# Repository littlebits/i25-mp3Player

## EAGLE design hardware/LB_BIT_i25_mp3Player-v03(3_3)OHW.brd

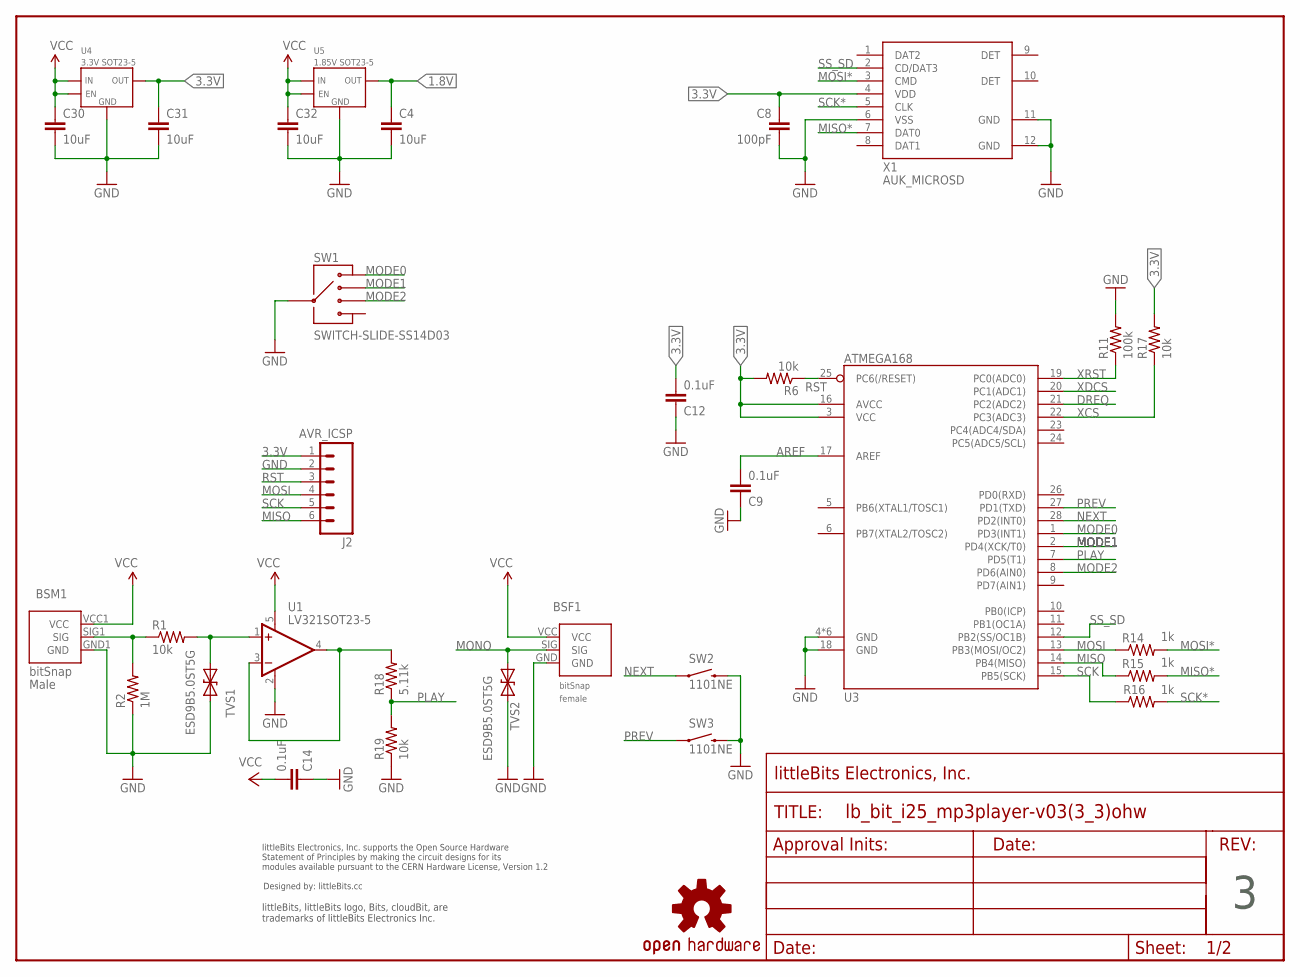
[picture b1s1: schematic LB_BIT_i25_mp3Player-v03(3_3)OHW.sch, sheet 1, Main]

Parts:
BSF1: BITSNAP_V03_FEMALE
BSM1: BITSNAP_V03_MALE
C4, C30, C31, C32: 10uF; CAP-0603
C8: 100pF; CAP-0603
C9, C12: 0.1uF; CAP-0402
C14: 0.1uF; CAP-0603
J2: AVR_ICSP; SIP6-SM-0.1IN-NOS.S-MIN
R1, R6, R17, R19: 10k; RES-0603
R2: 1M; RES-0603
R11: 100k; RES-0603
R14, R15, R16: 1k; RES-0603
R18: 5.11k; RES-0603
SW1: SWITCH-SLIDE-SS14D03; SWITCH-SLIDE-SP4T-SS14D03
SW2, SW3: 1101NE; TACTILE-SWITCH-1101NE
TVS1, TVS2: ESD9B5.0ST5G; SOD-923
U1: LV321SOT23-5; SOT23-5
U3: ATMEGA168; VQFN28
U4: 3.3V SOT23-5; SOT23-5
U5: 1.85V SOT23-5; SOT23-5
U$1: OSHWCREDIT
U$2: OSHW-LOGOL; OSHW-LOGO-L
U$38: FRAME-LETTER-OHWOHW; FABDWG01-OHW
X1: AUK_MICROSD; AUK_TFC08WP01-R1K-H

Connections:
1.8V: C4.1, U5.5 (OUT); also elsewhere on the board
3.3V: C8.1, C12.2, C31.1, J2.1, R6.2, R17.2, U3.3 (VCC), U3.16 (AVCC), U4.5 (OUT), X1.4 (VDD); also elsewhere on the board
AREF: C9.2, U3.17 (AREF)
DREQ: U3.21 (PC2(ADC2)); also elsewhere on the board
GND: BSF1.GND, BSM1.GND1 (GND), C4.2, C8.2, C9.1, C12.1, C14.1, C30.2, C31.2, C32.2, J2.2, R2.1, R11.2, R19.1, SW1.COM, SW2.P$2 (2), SW3.P$2 (2), TVS1.2 (C), TVS2.2 (C), U1.2 (V-), U3.4 (GND), U3.18 (GND), U3.TH (GND), U3.TH@1 (GND), U3.TH@2 (GND), U3.TH@3 (GND), U3.TH@4 (GND), U4.2 (GND), U5.2 (GND), X1.6 (VSS), X1.11 (GND), X1.12 (GND); also elsewhere on the board
MISO: J2.6, R15.1, U3.14 (PB4(MISO))
MISO*: R15.2, X1.7 (DAT0); also elsewhere on the board
MODE0: SW1.1, U3.1 (PD3(INT1))
MODE1: SW1.2, U3.2 (PD4(XCK/T0))
MODE2: SW1.3, U3.8 (PD6(AIN0))
MONO: BSF1.SIG, TVS2.1 (A); also elsewhere on the board
MOSI: J2.4, R14.1, U3.13 (PB3(MOSI/OC2))
MOSI*: R14.2, X1.3 (CMD); also elsewhere on the board
unnamed: BSM1.SIG1 (SIG), R1.1, R2.2
unnamed: R1.2, TVS1.1 (A), U1.1 (+IN)
unnamed: R18.2, U1.3 (-IN), U1.4 (OUT)
NEXT: SW2.P$1 (1), U3.28 (PD2(INT0))
PLAY: R18.1, R19.2, U3.7 (PD5(T1))
PREV: SW3.P$1 (1), U3.27 (PD1(TXD))
RST: J2.3, R6.1, U3.25 (PC6(/RESET))
SCK: J2.5, R16.1, U3.15 (PB5(SCK))
SCK*: R16.2, X1.5 (CLK); also elsewhere on the board
SS_SD: U3.12 (PB2(SS/OC1B)), X1.2 (CD/DAT3)
VCC: BSF1.VCC, BSM1.VCC1 (VCC), C14.2, C30.1, C32.1, U1.5 (V+), U4.1 (IN), U4.3 (EN), U5.1 (IN), U5.3 (EN); also elsewhere on the board
XCS: R17.1, U3.22 (PC3(ADC3)); also elsewhere on the board
XDCS: U3.20 (PC1(ADC1)); also elsewhere on the board
XRST: R11.1, U3.19 (PC0(ADC0)); also elsewhere on the board

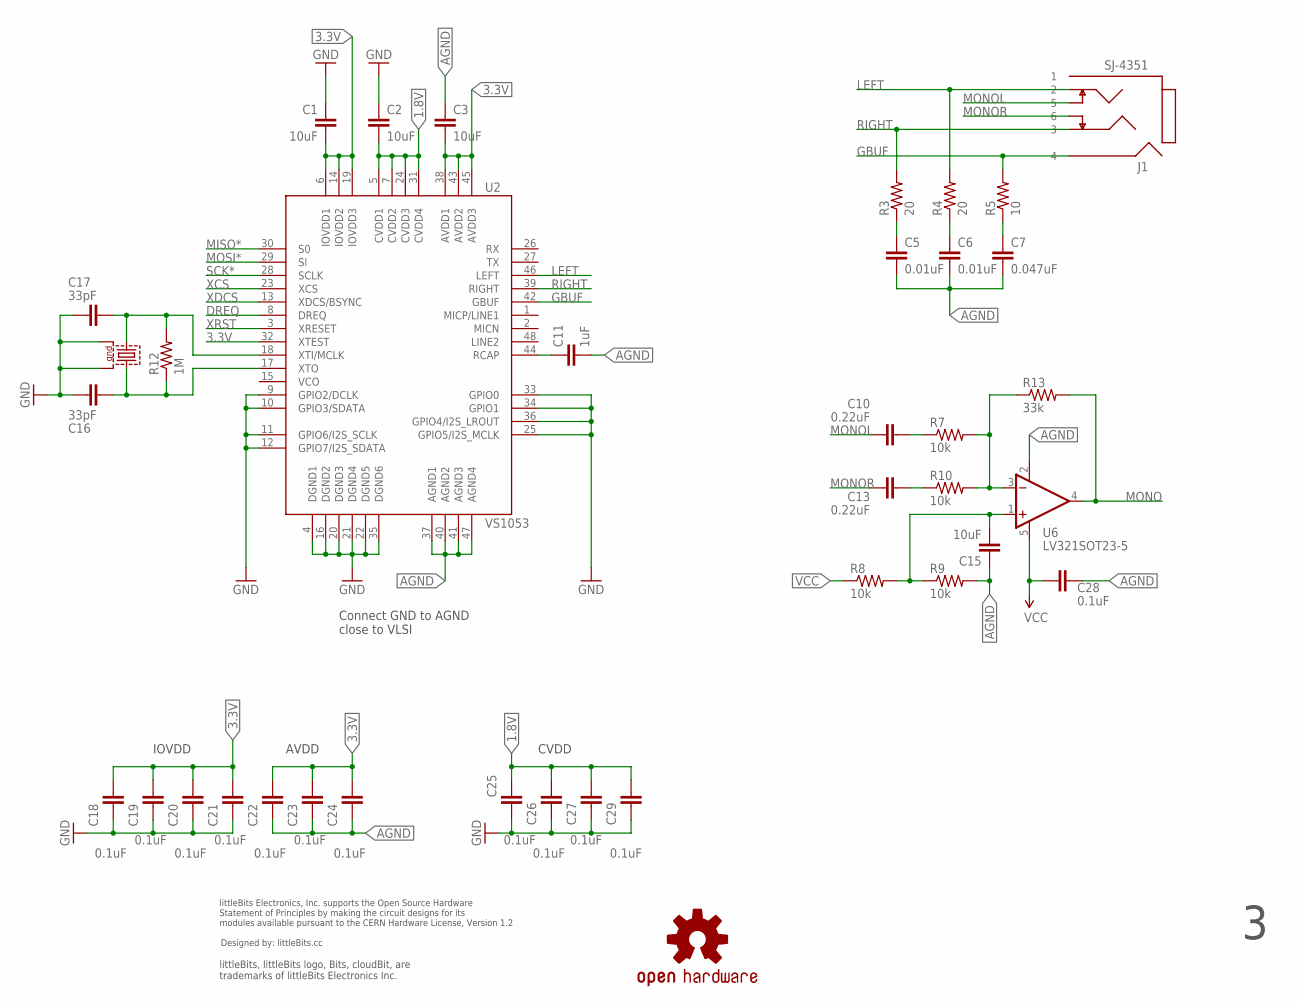
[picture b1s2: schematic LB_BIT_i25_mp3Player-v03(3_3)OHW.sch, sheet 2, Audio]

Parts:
C1, C2, C3, C15: 10uF; CAP-0603
C5, C6: 0.01uF; CAP-0603
C7: 0.047uF; CAP-0603
C10, C13: 0.22uF; CAP-0603
C11: 1uF; CAP-0402
C16, C17: 33pF; CAP-0603
C18, C19, C20, C21, C22, C23, C24, C25, C26, C27, C29: 0.1uF; CAP-0402
C28: 0.1uF; CAP-0603
J1: SJ-4351; CUI-SJ-4351
Q1: 12.288MHz; CRYSTAL-SMD-7B-SERIES-5X3.2MM
R3, R4: 20; RES-0603
R5: 10; RES-0603
R7, R8, R9, R10: 10k; RES-0603
R12: 1M; RES-0603
R13: 33k; RES-0603
U2: VS1053; LQFP-48
U6: LV321SOT23-5; SOT23-5
U$32: OSHWCREDIT
U$33: OSHW-LOGOL; OSHW-LOGO-L

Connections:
1.8V: C2.2, C25.1, C26.1, C27.1, C29.1, U2.5 (CVDD1), U2.7 (CVDD2), U2.24 (CVDD3), U2.31 (CVDD4); also elsewhere on the board
3.3V: C1.2, C3.2, C18.1, C19.1, C20.1, C21.1, C22.1, C23.1, C24.1, U2.6 (IOVDD1), U2.14 (IOVDD2), U2.19 (IOVDD3), U2.32 (XTEST), U2.38 (AVDD1), U2.43 (AVDD2), U2.45 (AVDD3); also elsewhere on the board
AGND: C3.1, C5.2, C6.2, C7.2, C11.2, C15.1, C22.2, C23.2, C24.2, C28.1, R9.2, U2.37 (AGND1), U2.40 (AGND2), U2.41 (AGND3), U2.47 (AGND4), U6.2 (V-)
DREQ: U2.8 (DREQ); also elsewhere on the board
GBUF: J1.4, R5.2, U2.42 (GBUF)
GND: C1.1, C2.1, C16.2, C17.2, C18.2, C19.2, C20.2, C21.2, C25.2, C26.2, C27.2, C29.2, Q1.P$2 (2), Q1.P$4 (4), U2.4 (DGND1), U2.9 (GPIO2/DCLK), U2.10 (GPIO3/SDATA), U2.11 (GPIO6/I2S_SCLK), U2.12 (GPIO7/I2S_SDATA), U2.16 (DGND2), U2.20 (DGND3), U2.21 (DGND4), U2.22 (DGND5), U2.25 (GPIO5/I2S_MCLK), U2.33 (GPIO0), U2.34 (GPIO1), U2.35 (DGND6), U2.36 (GPIO4/I2S_LROUT); also elsewhere on the board
LEFT: J1.2, R4.2, U2.46 (LEFT)
MISO*: U2.30 (S0); also elsewhere on the board
MONO: R13.2, U6.4 (OUT); also elsewhere on the board
MONOL: C10.2, J1.5
MONOR: C13.2, J1.6
MOSI*: U2.29 (SI); also elsewhere on the board
unnamed: R7.2, R10.2, R13.1, U6.3 (-IN)
unnamed: C6.1, R4.1
unnamed: C5.1, R3.1
unnamed: C7.1, R5.1
unnamed: C10.1, R7.1
unnamed: C13.1, R10.1
unnamed: C16.1, Q1.P$3 (3), R12.1, U2.17 (XTO)
unnamed: C11.1, U2.44 (RCAP)
unnamed: C17.1, Q1.P$1 (1), R12.2, U2.18 (XTI/MCLK)
RIGHT: J1.3, R3.2, U2.39 (RIGHT)
SCK*: U2.28 (SCLK); also elsewhere on the board
VCC: C28.2, R8.1, U6.5 (V+); also elsewhere on the board
VREF: C15.2, R8.2, R9.1, U6.1 (+IN)
XCS: U2.23 (XCS); also elsewhere on the board
XDCS: U2.13 (XDCS/BSYNC); also elsewhere on the board
XRST: U2.3 (XRESET); also elsewhere on the board

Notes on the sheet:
IOVDD
CVDD
AVDD
Connect GND to AGND close to VLSI

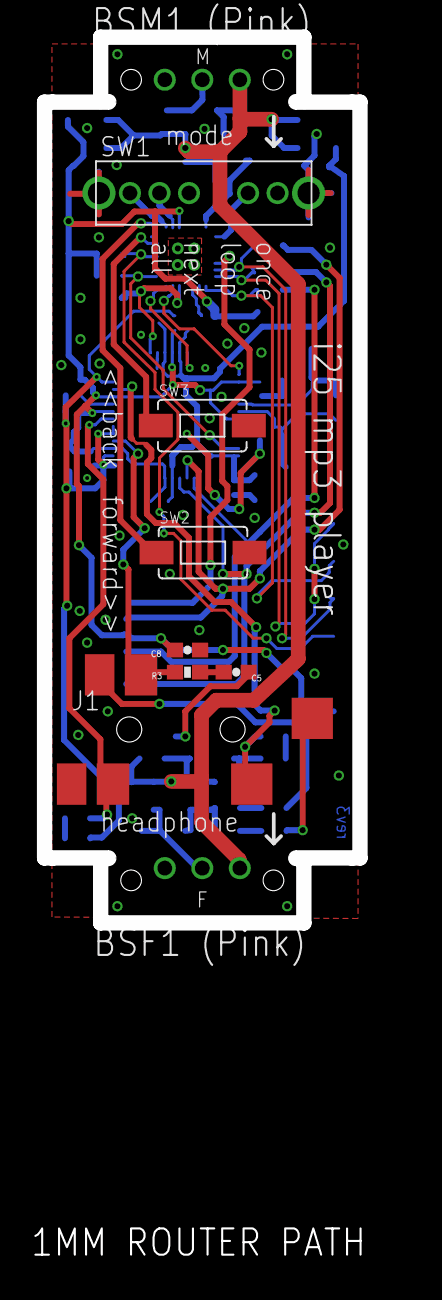
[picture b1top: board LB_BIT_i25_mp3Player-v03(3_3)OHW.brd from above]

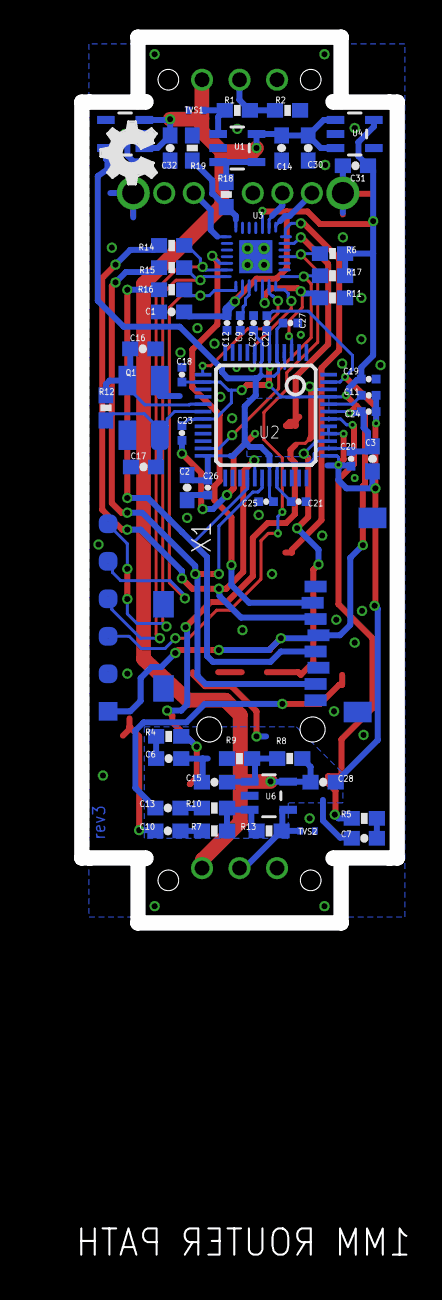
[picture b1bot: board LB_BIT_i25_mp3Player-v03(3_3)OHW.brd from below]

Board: 2 copper layers, 21.4 x 60.0 mm, 75 parts (59 on the bottom side), 43 nets.

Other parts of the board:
DRILEGEND: DRILEGEND
U$19: OSHW_FILLX150_NOTEXT

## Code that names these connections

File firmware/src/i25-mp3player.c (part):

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#define HOW_LONG_TO_CONSIDER_A_LOGIC_HIGH_INPUT_TO_BE_INTERPRETED_AS_A_LATCH_IN_MILLISECONDS 700

// Define our input buttons
#define PUSH_PLAY	(PIND & 0b00100000) >> 5	// PLAY/PAUSE BUTTON (SIG IN) set to PD5
#define PLAY_MODE	( (PIND & 0b01000000) >> 4 ) | ( (PIND & 0b00011000) >> 3) 	// THREE MODE SWITCH set to PD4/PD3
#define PREV		(PIND & 0b00000010) >> 1	// PREV FILE TACT BUTTON set to PD1
#define NEXT		(PIND & 0b00000100) >> 2	// NEXT FILE TACT BUTTON set to PD2

#define RESET_PIN	(0b00000001) //defines the RESET_PIN register space.

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U16 leftbytes; //total bytes left
U8 *buffer; //buffer
U32 sector; //record the current sector to judge the end sector
U16 TrackNumber=1;	//play the fist TrackNumber by default
U8 mode = 0;
U8 bPlay; //monitor for changes on the play/pause pint
U16 VolumeLevel = HEADPHONE_VOLUME_LEVEL;
U16 Q = 0; //Stall after dB change for no accidental track changes
U8 VolumeChanged = 0;
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					return 0;
				}	
				
				if((VS1053B_PIN & _BV(VS1053B_DREQ))!=0 && flag) //send data DREQ
				{
					
					wdt_reset();
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							P = 0;
							latchCount = 0; //Starts the latch timer
							if(flag) flag = 0; //if we are playing then pause
							else flag=1; //if we are paused then play
							loopOrAllInitialState = bPlay; //set out previous state
						}
						else if ( isLatched )
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							latchCount = 0;
							//latchDirection = bPlay;
							if(flag) flag = 0; //if we are playing then pause
							else flag=1; //if we are paused then play
							loopOrAllInitialState = bPlay; //set out previous state
						}
						else
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							P = 0;
							latchCount = 0; //Starts the latch timer
							if(flag) flag = 0; //if we are playing then pause
							else flag=1; //if we are paused then play
							loopOrAllInitialState = bPlay; //set out previous state
						}
						else if ( isLatched )
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							latchCount = 0;
							//latchDirection = bPlay;
							if(flag) flag = 0; //if we are playing then pause
							else flag=1; //if we are paused then play
							loopOrAllInitialState = bPlay; //set out previous state
						}
						else
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	U8 retry = 0;
	DDRD &= 0b00000000;		// set all PORTD pins as input
	PORTD |= 0b11111111;	// set pull-up resistors for all PORTD
	PORTD &= 0b11011111;	// clear pull-up resistor on PD5 (PLAY)
	
	OSCCAL = 0x00;	// Slow the clock in case it is too fast for some SD cards
	
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			latchCount = 0xFFFF;
			latchDirection = bPlay;
			//if(flag) flag = 0; //if we are playing then pause
			//else flag=1; //if we are paused then play
		}
	}
}
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
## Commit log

2014-11-18 First commit, added hardware and firmware
2015-01-08 Added second sch page to PDF

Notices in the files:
firmware/src/i25-mp3player.c:
Copyright 2014 littleBits Electronics
i25-mp3player is free software: you can redistribute it and/or modify
it under the terms of the GNU General Public License as published by
the Free Software Foundation, either version 3 of the License, or
(at your option) any later version.
parts and their libraries:
LITTLEBITS: modules available pursuant to the CERN Hardware License,
Version 1.2
LITTLEBITS: modules available pursuant to the CERN Hardware License, Version 1.2
